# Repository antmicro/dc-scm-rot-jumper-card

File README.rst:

=======================
DC-SCM RoT Jumper Board
=======================

Copyright (c) 2020-2022 `Antmicro <https://www.antmicro.com>`_

.. image:: img/rot-jumper-board.png

Overview
========

This repository contains open hardware design files for a simple jumper board which connects selected QSPI memories to the FPGA configuration interface on Antmicro's `Experimental DC-SCM card <https://github.com/antmicro/artix-dc-scm>`_.

Repository structure:
---------------------

The main repository directory contains the KiCad PCB project files, LICENSE and README.
The remaining files are stored in the following directories:

* ``img`` - contains graphics for this README
* ``lib`` - contains KiCad component libraries for the project

The design files were prepared in KiCad 5.1.9.

Key features
============

* Board-to-Board connector compatible with the DC-SCM card
* Jumper resistors for selecting the connection to one of the QSPI flash ICs located on the DC-SCM card

License
=======

`Apache-2.0 <LICENSE>`_

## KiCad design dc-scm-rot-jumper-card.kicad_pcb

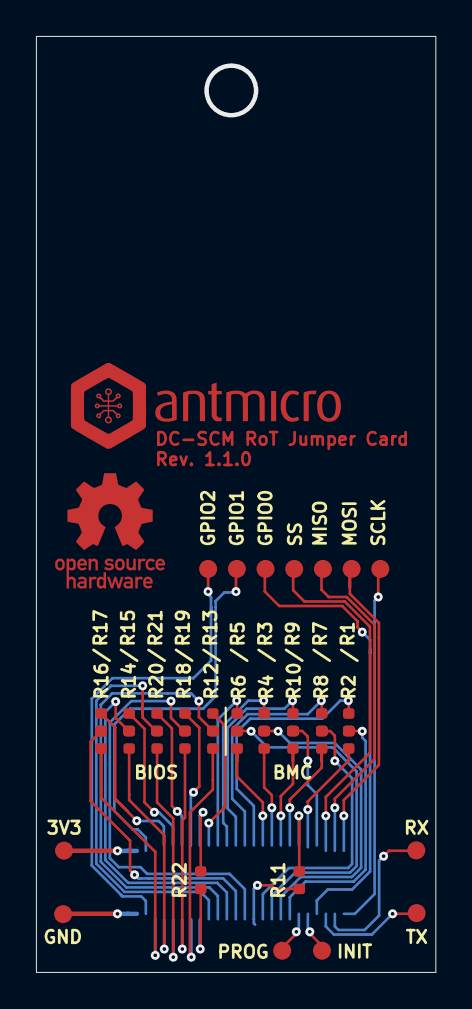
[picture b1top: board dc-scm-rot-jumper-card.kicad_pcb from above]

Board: 2 copper layers, 22.2 x 52.0 mm, 38 parts (1 on the bottom side), 47 nets.

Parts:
3V3: TP_SMD1MM; Testpoint_smd_1mm
GND: TP_SMD1MM; Testpoint_smd_1mm
GPIO0, GPIO1, GPIO2: TP_SMD1MM; Testpoint_smd_1mm
INIT: TP_SMD1MM; Testpoint_smd_1mm
J1: 5019205001
MISO: TP_SMD1MM; Testpoint_smd_1mm
MOSI: TP_SMD1MM; Testpoint_smd_1mm
N1: antmicro_logo; antmicro-logo_scaled_15mm
N2: oshw_logo; oshw-logo
PROG: TP_SMD1MM; Testpoint_smd_1mm
R1, R2, R3, R4, R5, R6, R7, R8, R9, R10, R11, R12, R13, R14, R15, R16, R17, R18, R19, R20, R21, R22: R_0R_0402; 0402-res
RX: TP_SMD1MM; Testpoint_smd_1mm
SCLK: TP_SMD1MM; Testpoint_smd_1mm
SS: TP_SMD1MM; Testpoint_smd_1mm
TX: TP_SMD1MM; Testpoint_smd_1mm

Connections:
GND: GND.1, J1.26, J1.27
INIT: INIT.1, J1.46
PROGRAM: J1.45, PROG.1
QSPI0_CLK: J1.34, R22.1
QSPI0_CS0_N: J1.35, R20.1, R21.1
QSPI0_D0: J1.36, R12.1, R13.1
QSPI0_D1: J1.37, R14.1, R15.1
QSPI0_D2: J1.38, R16.1, R17.1
QSPI0_D3: J1.39, R18.1, R19.1
QSPIA1_CS_N: J1.31, R20.2
QSPIA1_D0: J1.33, R12.2
QSPIA1_D1: J1.30, R14.2
QSPIA1_D2: J1.29, R16.2
QSPIA1_D3: J1.32, R18.2
QSPIA2_CS_N: J1.7, R21.2
QSPIA2_D0: J1.10, R13.2
QSPIA2_D1: J1.6, R15.2
QSPIA2_D2: J1.5, R17.2
QSPIA2_D3: J1.8, R19.2
QSPIA_CLK: J1.9, R22.2
QSPIB1_CS_N: J1.13, R9.2
QSPIB1_D0: J1.15, R1.2
QSPIB1_D1: J1.12, R3.2
QSPIB1_D2: J1.11, R5.2
QSPIB1_D3: J1.14, R7.2
QSPIB2_CS_N: J1.18, R10.2
QSPIB2_D0: J1.21, R2.2
QSPIB2_D1: J1.17, R4.2
QSPIB2_D2: J1.16, R6.2
QSPIB2_D3: J1.19, R8.2
QSPIB_CLK: J1.20, R11.2
ROT_GPIO1: GPIO1.1, J1.3
ROT_GPIO2: GPIO2.1, J1.28
ROT_MISO: J1.24, MISO.1
ROT_MOSI: J1.25, MOSI.1
ROT_QSPI_CS_B: J1.22, R9.1, R10.1
ROT_QSPI_DQ0: J1.44, R1.1, R2.1
ROT_QSPI_DQ1: J1.43, R3.1, R4.1
ROT_QSPI_DQ2: J1.42, R5.1, R6.1
ROT_QSPI_DQ3: J1.41, R7.1, R8.1
ROT_QSPI_SCK: J1.40, R11.1
ROT_RDY\ROT_GPIO0: GPIO0.1, J1.47
ROT_RX: J1.49, RX.1
ROT_SCLK: J1.50, SCLK.1
ROT_SS: J1.23, SS.1
ROT_TX: J1.48, TX.1
VCC3V3: 3V3.1, J1.1, J1.2

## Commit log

2022-01-13 Cleanup
2022-01-13 Add LICENSE
2022-01-13 Add README
2022-01-13 README: minor updates
